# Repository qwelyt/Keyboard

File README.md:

# Keyboard
I'm building my own keyboard.
It's as simple as that.

Why? Because I want to. And I've yet to find a keyboard that looks the way I want it to. The solution seems to be to build your own. So that's what I'm doing.

## Layout
The layout is a split keyboard with the keys in a matrix. Here's a pic (v2)

### Why split?
Every keyboard I've tried have always forced you to put your hands inwards, in a / \ way (pretend that's your arms). But I want to be able to keep my arms like | | or even \ /. With a split keyboard where you can move each module to where you want it to be you can achive this. I *think* this would give you better ergonomics, but we'll see. We might be using the one-module-fits-all approach for more than just cheaper-to-produce reasons. But if you never try, you never know.

### Why a linear matrix layout?
As far as I've found, the only reason we use keyboards with slanted columns is because 'it has always been like that'. Like, from the typewriter-era. And then it was for mechanical reasons. But now that we no longer have metal arms that must be physically fit into the layout, we can design it just as we want. And apparently the slanted-columns-layout is bad for you. You stretch your fingers in an un-natural way which puts strain on your limbs and increases the odds of injury.
That is just bad. So I'm going for a linear matrix layout because I like my fingers. They should have the best typing experiance they can have.

### Raise and Lower?
Do you really use *F1* so much that it needs its own dedicated key? I don't. So tucking it away under *Raise*+*1* works well. I think. Also, doing it layered gives you way more keys than you actually have. Take module A. It has 30 keys. 2 of which are layer modifiers. This gives me 28 keys to play with, in three layers. So I actually got 28x3 keys, so thats 84 keys in total. I probably won't use that many, but it is nice to have the possibility. Mainly though, it cuts down on parts used and size, which is a big things given that 3D-printers (or at least mine) can't print super-mega-big things. 
Credit where it is due: The Planck keyboard has this (https://youtu.be/bEPg8kk84gw) which influenced me to have it as well.

## Parts
This build is my first keyboard that I'm building from scratch. I've done a few mods, but never a complete build.
To build this I'm using some mechanical switches (Black ALPS) that I 'rescued' from a to-be-thrown Dell AT101. I've got 104 keys from that old keyboard. Most of which still have the click sound. And I have the caps, ofc.

The modules cases is made to be 3D printed. I use a FlashForge Finder to print.

It's NKRO, so there is an 1N4149 diode for every switch.

The controller is an Arduino Micro (https://store.arduino.cc/arduino-micro).

Each module will be it's own keyboard. Meaning, each module will has it's own controller. So you don't need to plug in A to be able to use B and vice versa. This ofc means that, for 2 modules, you need 2 USB ports. One could build a USB hub as well to plug the modules into. Makes for a cleaner setup as you will only need 1 cable going to the computer. Might try building in retractable cables in everything if I take a stab at it, but well see how much of a pain that is.

# Log
| Todo | Doing | Done |
|------|-------|------|
||| Create basic working matrix |
||| Create 3D sketches for modules |
|||Create schematics for matrix |
|||Get hands on a 3D printer|
||| Get diods |
||| Print test module |
||| Assemble test module |
||| Code test module |
||| Get real controller board |
||| Refactor |
||| Print module A |
||| Print module B |
||| Assemble A |
||| Assemble B |
||| Code A |
||| Code B |
|| ??? || 
| Refactor|||
| Profit|||

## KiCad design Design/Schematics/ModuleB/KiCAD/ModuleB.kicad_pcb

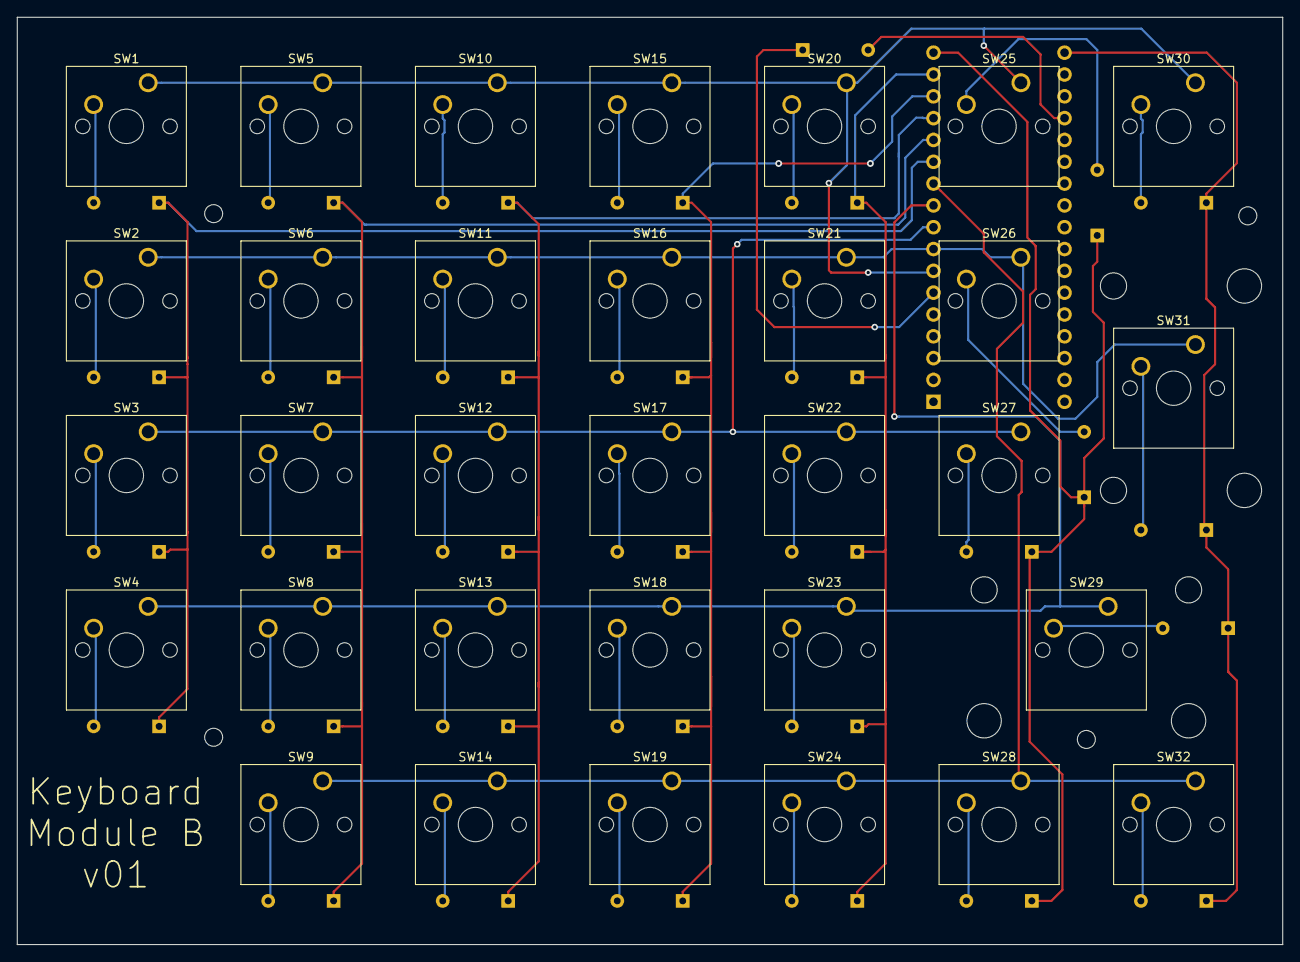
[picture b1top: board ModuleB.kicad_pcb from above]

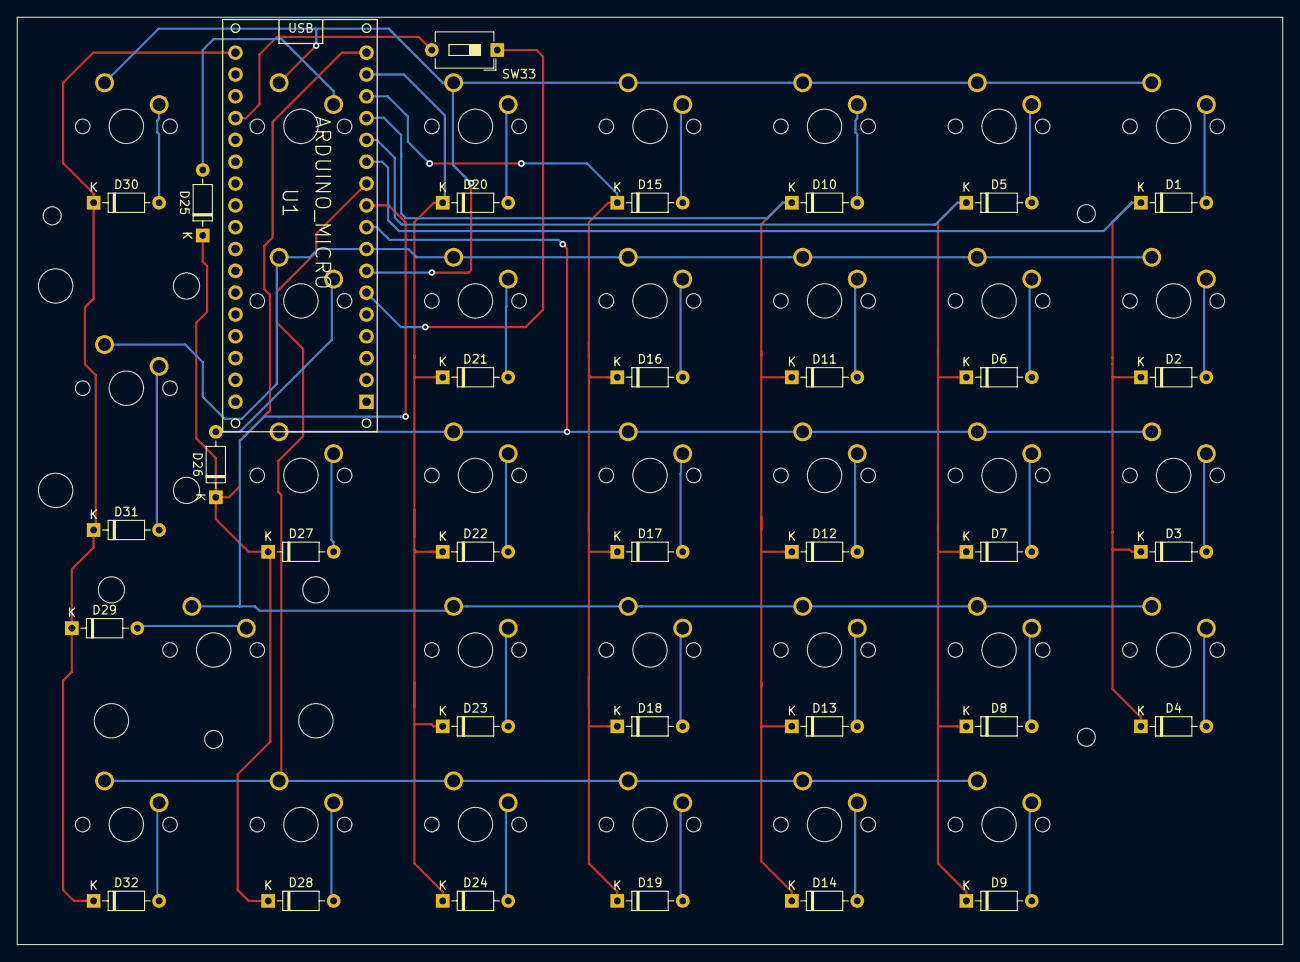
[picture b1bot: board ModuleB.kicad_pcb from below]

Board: 2 copper layers, 147.3 x 107.9 mm, 66 parts (34 on the bottom side), 46 nets.

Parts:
D1, D2, D3, D4, D5, D6, D7, D8, D9, D10, D11, D12, D13, D14, D15, D16, D17, D18, D19, D20, D21, D22, D23, D24, D25, D26, D27, D28, D29, D30, D31, D32: 1N4149; D_DO-35_SOD27_P7.62mm_Horizontal
SW1, SW2, SW3, SW4, SW5, SW6, SW7, SW8, SW9, SW10, SW11, SW12, SW13, SW14, SW15, SW16, SW17, SW18, SW19, SW20, SW21, SW22, SW23, SW24, SW25, SW26, SW27, SW28, SW30, SW32: SW_Push; SW_Cherry_MX1A_1.00u_PCB
SW29: SW_Push; SW_Cherry_MX1A_2.00u_PCB
SW31: SW_Push; SW_Cherry_MX1A_2.00u_Vertical_PCB
SW33: SW_Push; SW_DIP_SPSTx01_Slide_6.7x4.1mm_W7.62mm_P2.54mm_LowProfile
U1: ARDUINO_MICRO; ARDUINO_MICRO_SHIELD

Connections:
unnamed: D1.1, D2.1, D3.1, D4.1, U1.7
unnamed: D1.2, SW1.2
unnamed: D2.2, SW2.2
unnamed: D3.2, SW3.2
unnamed: D4.2, SW4.2
unnamed: D5.1, D6.1, D7.1, D8.1, D9.1, U1.8
unnamed: D5.2, SW5.2
unnamed: D6.2, SW6.2
unnamed: D7.2, SW7.2
unnamed: D8.2, SW8.2
unnamed: D9.2, SW9.2
unnamed: D10.1, D11.1, D12.1, D13.1, D14.1, U1.9
unnamed: D10.2, SW10.2
unnamed: D11.2, SW11.2
unnamed: D12.2, SW12.2
unnamed: D13.2, SW13.2
unnamed: D14.2, SW14.2
unnamed: D15.1, D16.1, D17.1, D18.1, D19.1, U1.10
unnamed: D15.2, SW15.2
unnamed: D16.2, SW16.2
unnamed: D17.2, SW17.2
unnamed: D18.2, SW18.2
unnamed: D19.2, SW19.2
unnamed: D20.1, D21.1, D22.1, D23.1, D24.1, U1.11
unnamed: D20.2, SW20.2
unnamed: D21.2, SW21.2
unnamed: D22.2, SW22.2
unnamed: D23.2, SW23.2
unnamed: D24.2, SW24.2
unnamed: D25.1, D26.1, D27.1, D28.1, U1.12
unnamed: D25.2, SW25.2
unnamed: D26.2, SW26.2
unnamed: D27.2, SW27.2
unnamed: D28.2, SW28.2
unnamed: D29.1, D30.1, D31.1, D32.1, U1.13
unnamed: D29.2, SW29.2
unnamed: D30.2, SW30.2
unnamed: D31.2, SW31.2
unnamed: D32.2, SW32.2
unnamed: SW1.1, SW5.1, SW10.1, SW15.1, SW20.1, SW25.1, SW30.1, U1.2
unnamed: SW2.1, SW6.1, SW11.1, SW16.1, SW21.1, SW26.1, SW31.1, U1.3
unnamed: SW3.1, SW7.1, SW12.1, SW17.1, SW22.1, SW27.1, U1.4
unnamed: SW4.1, SW8.1, SW13.1, SW18.1, SW23.1, SW29.1, U1.5
unnamed: SW9.1, SW14.1, SW19.1, SW24.1, SW28.1, SW32.1, U1.6
unnamed: SW33.1, U1.GND
unnamed: SW33.2, U1.A0

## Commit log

2016-10-02 Fix ignore on vim-files.
2016-10-02 Add design and SCAD files.
2016-10-02 Update ignore to allow hex. Added basic code. Added hex files needed for arduino UNO to be able to act as a keyboard (and arduino again). Added basic code for a numpad and som basic alphas. Also adde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
2016-10-02 Add PDF for the USB HID stuff. So I know which code to send for which key.
2016-10-02 Update readme.
2016-10-02 Add pic
2016-10-03 Inline picture.
2016-10-03 Added info to readme.
2016-10-09 Update readme with a table.
2016-10-09 Moved and renamed files. Put together a basic build of moduleA. No holes for USB done. Will see how this prints later. A bit worried about the integrity of the top part. Wondering if it will stay rig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
2016-10-09 Add the stl for moduleA build.
2016-10-12 Add thing to do.
2016-10-22 Add matrix schematics for the test code.
2016-10-22 Get images from Fritzing.
2016-10-22 Move fritzproject to matrix dir.
2016-12-22 Add work on ModuleA
2016-12-23 Start working on the code for ModuleA.
2016-12-26 Change to enum and start naming keys.
2016-12-27 ModuleA is shaping up. Segfaults ArduinoIDE when compiling though.
2016-12-27 Move mod-values to an enum. And set correct returntype on metaValue. Also, the compiler doesn't segfault now.
2017-01-05 Fix typo that turned out to be a major bug.
2017-05-07 Add print tests for key-sizes. The keys must fit the holes, obviously..
2017-05-13 Add structure to the top so it doesn't bend.
2017-05-14 New moduleA with a new design that should require fewer keys.
2017-05-14 Update the lod
2017-05-14 Update the log
2017-05-14 Add svg of new layout
2017-05-21 Add layoutV2 png
2017-05-21 New layout, and Raise and lower.
2017-05-21 ModuleBv2 is ready for the printers.
2017-07-11 Update log
2017-07-13 Organising and adding a new v2 for the code.
2017-07-14 Working ModuleA for the Arduino Micro. Woop!
2017-07-14 Refacoring to less code. Does the same thing.
2017-07-15 V2 of the breadboard. Wire it like this.
2017-07-19 Add spacer to A. A wall, basically.
2017-07-22 Add arduino Micro holder, a bottom plate, and an STL file with everything put together. That one should not be printed. Also updates to teh frizing file.
2017-07-22 Remove merge info.
2017-07-22 Add STL of whole moduleA. DO NOT PRINT THIS! ONLY FOR SHOW!
2017-07-22 Turn the holder the other way. No reason to have it upside down. Also add screw holes so you can hold it securely in place.
2017-08-20 Switched places on A:s Alt. Rotate a key on B.
2017-08-20 Better design of the whole module, I think...
2017-10-06 Module B breadboard layout. Uses the same pins as A, which is nice.
2017-10-06 Start work on how the layerd code should be (not done), also add the printing design for ModuleB. Since the bottom is the same as ModA, only the top layer is what differs between them. Might put them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
2017-10-30 Layers work. No work on media keys though. They seem to be a bit tricky. Need to assign a new controller for them, in software, like they have their own ID and stuff. Need to investigate how to do it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
2017-11-13 Add svg for module B.
2017-11-13 Add show-off pics.
2017-11-13 Make ModuleB work.
    The only difference between A and B is the layout.
    Otherwise thay are exactly the same.
2017-11-13 Add more available keys.
2017-12-11 Change layout a bit.
2017-12-11 Add print screen key
2019-04-07 Add KiCAD files
    Would be fun to actually make a PCB for the keyboard instead of
    handwireing. Taking a stab at using KiCAD for the desing. Seems to be a
    program that fits my needs. PCB design can be finickey I noticed...

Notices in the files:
Design/Schematics/ModuleB/KiCAD/ModuleB.kicad_pcb:
License: GNU GPLv3
